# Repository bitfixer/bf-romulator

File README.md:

# bf-romulator
Romulator - RAM/ROM replacement and debug for 6502 and Z80 CPU systems

romulator - verilog code to implement ROMulator RAM/ROM replacement

programmer - programmer and console application for updating ROMulator, and debug

tools - C++ tools for building firmware images for ROMulator

## About

The ROMulator is a RAM/ROM replacement device for 6502 and Z80 systems, with programmable memory maps and debug functionality which allows you to halt a running CPU and read from or write to memory. See https://bitfixer.com/romulator for more information.

This Readme mostly covers the 6502 version for now, more documentation coming soon for Z80.

## Installation

To use the ROMulator, first remove the 6502 CPU from its socket on the PET (or other computer)'s motherboard.
**Note the orientation of the notch on the 6502 chip in the socket.**
Insert the 6502 chip into the 40-pin socket on the ROMulator board. Make sure the notch on the chip is aligned with the notch on the ROMulator socket.
Then, take the ROMulator board, and using the pins on the underside of the board, insert it into the 6502 socket on the motherboard.
**Make sure the notch on the 6502 chip is pointing in its original direction.**
If the ROMulator is inserted backwards, this may damage the ROMulator board since 5v will be presented where it shouldn't be.
Just make sure to double check:
- Original orientation of 6502
- 6502 chip notch should match with notch in ROMulator socket
- When inserting ROMulator into 6502 socket, 6502 chip should be in its original orientation

## Default Switch Settings

The ROMulator supports up to 32 memory maps. The default memory maps shipped with the ROMulator are currently mostly related to the Commodore PET, but you can add any maps you want via the programming interface. Over time more configurations for common 6502 computers will be added. Please note that these settings reflect the head commit of the repository, and may differ from the default settings on your ROMulator depending on when it was programmed. Building the latest version with `make program` after a `git pull` will generate the settings as described.
The default switch settings are as follows:

|Set Index  |Setting                                        |Switch 1   |Switch 2   |Switch 3   |Switch 4   |
|-----------|-----------------------------------------------|-----------|-----------|-----------|-----------|
|0          |BASIC 2, NON-CRTC, Business Kbd  (i.e. 2001)   |Off        |Off        |Off        |Off        |
|1          |BASIC 4, NON-CRTC  (i.e. 2001)                 |On         |Off        |Off        |Off        |
|2          |BASIC 4, CRTC, 80C (i.e. 8032)                 |Off        |On         |Off        |Off        |
|3          |BASIC 4, CRTC, 40C (i.e. 4032,4016)            |On         |On         |Off        |Off        |
|4          |BASIC 4, PET 4032 60Hz                         |Off        |Off        |On         |Off        |
|5          |BASIC 2, NON-CRTC, Normal Kbd (i.e. 2001)      |On         |Off        |On         |Off        |
|6          |BASIC 4, PET 4032 50Hz                         |Off        |On         |On         |Off        |
|7          |BASIC 4, PET 4016 60Hz                         |On         |On         |On         |Off        |
|8          |Apple II plus                                  |Off        |Off        |Off        |On         |
|9          |BASIC 1, PET 2001-8                            |On         |Off        |Off        |On         |
|10         |VIC-20 PAL                                     |Off        |On         |Off        |On         |
|11         |VIC-20 NTSC                                    |On         |On         |Off        |On         |
|12         |NOP Generator                                  |Off        |Off        |On         |On         |
|13         |PETTESTER                                      |On         |Off        |On         |On         |
|14         |PET Low RAM Test                               |Off        |On         |On         |On         |
|15         |PET RAM/ROM/VRAM Test                          |On         |On         |On         |On         |

The memory maps are defined in [config/memory_set_default.csv](config/memory_set_default.csv).
This file indicates which ROMs are located at which memory address.

## Adding Configurations for New 6502 Machines

This topic is big enough to have its own readme, and it is located here:\
[config/README.md](config/README.md)

## Program / Debug

Programming and Debugging with the ROMulator can be done in one of two ways:
- using a Raspberry Pi connected to the ROMulator's 10-pin header, or
- using a standalone programmer consisting of a D1 Mini Board (dev board for ESP12 wifi microcontroller module) and an interface board for connecting to the ROMulator. This method allows uploading new firmware over a wifi network as well as a direct connection to a Win/Linux/Mac using usb.

### Program / Debug with Standalone Programmer over WiFi or USB
Information on programming and debugging using the standalone programmer can be found here:\
[ROMULATOR_STANDALONE.md](ROMULATOR_STANDALONE.md)

### Program / Debug with Raspberry Pi
Programming or Debug functionality of the ROMulator uses a Raspberry Pi using a soft SPI implementation. 
You can use the optional RPI ROMulator programming board, or directly connect the following RPI physical pins to the corresponding pins on the 10-pin header on the ROMulator FPGA board:

|RPI     |FPGA Hdr|FPGA Hdr |RPI |
|--------|--------|---------|----|
|19      |1 (MOSI)|2 (3.3v) |17  |
|24      |3 (CS)  |4 (DBG)  |36  |
|22      |5 (RST) |6 (CDONE)|11  |
|23      |7 (SCK) |8        |NC  |
|21      |9 (MISO)|10 (GND) |34  |

If you are only programming and not running the debug client, DBG and CDONE are optional.
Take a look at this wiring diagram for a visual aid:

# ROMulator programming board

The optional RPI ROMulator programming board is just a breakout board for SPI and UART on the Pi which brings SPI0 and SPI1 pins out to separate headers, as well as a UART header. The ROMulator only uses the SPI0 header. If you received a kit for this board, here are a few quick notes on the assembly.
1. Solder header pins onto the TOP of the board in the section marked 'SPI0'.
2. Solder a 2-pin header onto the header section directly adjacent to SPI0.
3. Solder the 2x20 socket onto the BOTTOM of the board.
4. Connect the jumper onto the 2-pin header for programming. Remove for debug.
5. When attaching the board to the raspberry pi, the headers face away from the body of the raspberry pi. Depending on how the connectors are attached to the ribbon cable, it may be connected in one of two ways. Just make sure there is no twist in the cable. See these images for reference:

<table>
  <tr>
    <td>If your cable looks like this:</td>
    <td>Connect it like this.</td>
  </tr>
  <tr>
    <td></td>
    <td></td>
  </tr>
</table>

Or,

<table>
  <tr>
    <td>If your cable looks like this:</td>
    <td>Connect it like this.</td>
  </tr>
  <tr>
    <td></td>
    <td></td>
  </tr>
</table>

Please follow this procedure to enter debug mode on the romulator and read the contents of a running CPU.
1. run ```make bin/console``` from bf-romulator directory
2. run ```make debug``` to set appropriate pin directions on the pi. Specifically, this sets the DBG line to 1 to allow the ROMulator to start and not be stuck in a halt state, and sets the RST line to an input to avoid holding the fpga in reset.
3. If you are using the optional RPI programming board, remove the programming jumper.
4. run ```bin/console -r > output.bin``` to halt the cpu and read the full memory map into a file called output.bin.

### Installation

To install the ROMulator software on a Raspberry PI for programming or debug, download the script [setup.sh](https://raw.githubusercontent.com/bitfixer/bf-romulator/master/setup.sh) onto your Pi and execute from your home directory.
This will install the prequisites and fetch the latest version of the code in this repo.

The one-liner for this on the command line is:\
```wget -O - https://raw.githubusercontent.com/bitfixer/bf-romulator/master/setup.sh | sudo bash```

### Programming

To program a new firmware onto the ROMulator, run\
```make program```\
from the ~/bf-romulator directory.

Note that you will need all of the roms present in order to complete the build.\
This means that every unique rom specified in [config/memory_set_default.csv](config/memory_set_default.csv) to be present in the bf-romulator/roms directory.\
For convenience if you are downloading ROM images from a single source, there is a script which will do this for you.\
If you were downloading every rom with the base url of http://bitfixer.com, you would run the command:\
```BASEURL=http://bitfixer.com make fetch_roms```\
This downloads every unique rom specified in [config/memory_set_default.csv](config/memory_set_default.csv) to the roms directory.

## Programming Custom Firmware

If you just want to program a custom .bin file (if I send you one, for example) the procedure is a bit simpler.
Before the first time doing this run\
```make bin/programmer_spi```\
from the ~/bf-romulator directory.

Then, copy the custom .bin file somewhere on your raspberry pi, and run\
```bin/programmer_spi < customfirmware.bin```\
from the ~/bf-romulator directory, replacing customfirmware.bin with the actual path of that file.

## Virtual Display

A recent feature added to the ROMulator is the ability to create a virtual external display, using a connected Raspberry Pi as a webserver. By pointing a browser to the pi server, you will be able to 'see' the contents of video ram in realtime rendered into bitmap images.\
Currently, only the PET 2001 is supported, but other 6502 machines with memory-mapped graphics will be added soon.\
To use the virtual display feature on a PET 2001, connect the ROMulator to the 6502 socket on the pet, and connect the Pi via the interface board with the programming jumper OFF. For now only setting 1 (Sw 1 ON, rest OFF) is supported, which is BASIC 4.\
Power up the PET as usual, and the ROMulator LED should blink on for about one second. Then from the console on your Pi, from the bf-romulator directory, run:\
```make webserver```\
Then open a browser on another computer on the same network as the Pi, and navigate to the pi's server, like so:\
```http://raspberrypi.local:10000/canvas.html```\
Please note that while the pi will usually show up as raspberrypi.local, this is not always the case and you may need to know the actual local IP. At this point you should be able to enjoy a roughly 15-20 FPS PET 2001 display in your browser!

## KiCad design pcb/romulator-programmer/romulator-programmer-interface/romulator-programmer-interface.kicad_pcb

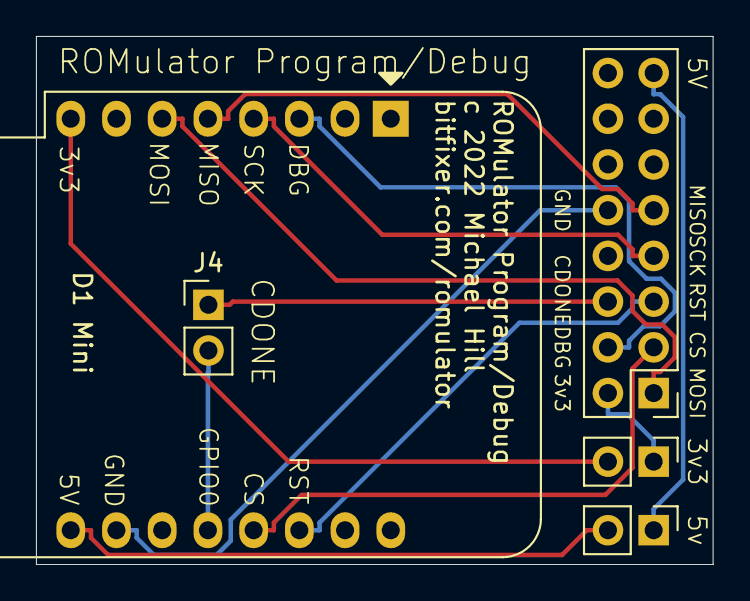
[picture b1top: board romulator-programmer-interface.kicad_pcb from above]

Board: 2 copper layers, 37.6 x 29.3 mm, 5 parts (0 on the bottom side), 13 nets.

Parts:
J1, J2, J4: Conn_01x02_Male; PinHeader_1x02_P2.54mm_Vertical
J3: Conn_02x08_Odd_Even; PinHeader_2x08_P2.54mm_Vertical
U1: WeMos_D1_mini; WEMOS_D1_mini_light

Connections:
3v3IN: J1.2, U1.8
5VIN: J2.2, U1.9
+3V3: J1.1, J3.2
+5V: J2.1, J3.15
CDONE: J3.6, J4.1
CS: J3.3, U1.13
DBG: J3.4, U1.3
GND: J3.10, U1.10
GPIO0: J4.2, U1.12
MISO: J3.9, U1.5
MOSI: J3.1, U1.6
RST: J3.5, U1.14
SCK: J3.7, U1.4

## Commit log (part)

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2020-01-21 installation script
2020-01-21 added verilog files
2020-01-21 added tools
2020-01-21 added pin constraints
2020-01-21 changed data_out to reg
2020-01-21 adding makefile
2020-01-21 added programmer
2020-01-21 updated common makefile
2020-01-21 updated makefile
2020-01-22 added romulator target
2020-01-22 removed unused files
2020-01-22 fixed makefile to prevent unnecessary rebuilds
2020-01-23 use full 64k maps
2020-01-23 increase to full 16 memory maps
2020-01-23 updated to 16 configurations
2020-01-23 fixed build_enable_table
2020-01-23 updated configuration size
2020-01-23 updated flash reader
2020-01-24 added GPL license
2020-01-24 license in Makefile
2020-01-24 added board schematics
2020-01-25 added rpi programming board schematic
2020-01-26 modified setup script
2020-01-26 fix table
2020-01-29 added reset option
2020-02-01 added README
2020-02-24 changed memory enable granularity
2020-02-24 change rom directory
2020-02-24 updated fetch_roms
2020-02-24 fixed dir
2020-02-24 change 9000-AFFF passthrough region
2020-02-25 fixed install script, apio seems to be broken at later version?
2020-02-25 slow down read on programmer, prevent bit errors
2020-02-26 added modified edit roms for 8032
2020-02-26 log readback
2020-02-27 changed programmer pins
2020-02-27 added readback
2020-02-28 fixed Makefile
2020-02-28 added make_screen_image
2020-02-28 mod screen image util
2020-02-29 added webserver, test option for make_screen_image
2020-03-01 tested image loading through web interface
2020-03-03 added testing files
2020-03-03 added console test
2020-03-03 fixed filename
2020-03-03 adjust timing of console
2020-03-04 Testing1 (#1)
    * added testing files
    * fixed makefile
    * added console test
    * fixed filename
    * adjust timing of console
2020-03-04 remove random bin during clean
2020-03-04 Change granularity 2 (#2)
    * changed memory enable granularity
    * remove random bin during clean
    * Makefile
2020-03-04 moved random_test.bin
2020-03-04 updated to physical pin numbers
2020-03-04 updated programming pins in README
2020-03-04 update 3v3 pin
2020-03-04 added stub for crc32
2020-03-04 WIP fpga does crc on debug
2020-03-04 fixed name
2020-03-04 size
2020-03-04 transfer dummy byte
2020-03-05 oops
2020-03-05 show crc32 of test binary
2020-03-05 report mismatch
2020-03-05 Crc32 (#3)
    * added stub for crc32
    * fixed syntax
    * WIP fpga does crc on debug
    * fixed name
    * size
    * transfer dummy byte
2020-03-05 add verification during memory write, retries for read
2020-03-23 added custom editor memory set
2020-03-24 added spi
2020-03-24 added 2001 normal keyboard option
2020-03-24 fixed rom
2020-04-07 updated switch settings
2020-04-07 Mhill/update readme (#4)
    * fixed rom
    * updated switch settings
2020-05-01 for pets without B000 rom, enable passthrough for B000-BFFF
2020-05-04 update apio version
2020-05-04 reboot after setup
2020-09-19 halt cpu while loading from flash
2020-09-19 added memory map for apple ii plus
2020-09-23 memory maps for apple ii plus
2020-09-24 fixed issue with memory reader, in some cases the next byte was sent before the previous was finished
2020-09-25 add debug mode to makefile
2020-09-25 added tool to verify rom dump from running system
2020-10-02 added a test rom for testing motherboard roms
2020-10-02 added zero page test
2020-10-02 added makefile for test rom
2020-10-04 ram check works
2020-10-04 makefile updates
2020-10-04 fixed
2020-10-04 added test_pet program to simplify test execution
2020-10-06 cleaned up testrom code
2020-10-06 updated testrom and console test program
2020-10-06 fixed test_pet bug
2020-10-06 cleanup on test_rom
2020-10-06 added apple ii test program
2020-10-06 fixed target for test_appleii
2020-10-22 changed url of submodule
2020-12-09 added rockwell aim-65 roms
2020-12-11 added 16k option for 4016
2021-01-08 added pin state to enable starting in debug
2021-02-24 added target for webserver
2021-02-24 simplify Makefile
2021-02-24 moved webserver
2021-02-24 fix makefile
2021-02-24 fix makefile2
2021-03-23 added settings for a PET 2001-8 board
2021-03-24 started test program for ram rom test
2021-03-24 more ram test stuff
2021-03-25 zero page test works
2021-03-25 more work on ram test, added pettest rom
2021-03-25 more mem test stuff
2021-03-25 swapped x and y flags
2021-03-25 separate flip
2021-03-25 added pages to test
2021-03-26 cleanup test rom
2021-03-26 added display to mem test
2021-03-27 cleaning up ram tester
2021-03-27 add config file
2021-03-27 fixed display of fault info
2021-03-28 added new rom and vram tester
2021-03-28 ramtest compilation works
2021-03-29 fixed fetch rom script
2021-03-29 added ram and rom tests to pet 2001 setup
2021-03-29 added nop generator
2021-03-31 add preinit
2021-03-31 show checksum for every 2048 bytes
2021-03-31 fixed edit rom on basic 2,4
2021-05-06 added diag tools
2021-05-06 ram test set text mode
2021-05-06 added wiring diagram for programming and debug
2021-05-12 updated diagram
2021-05-12 added kicad project with programming diagram
2021-05-18 fixed end address on ram test
2021-06-21 link to tools readme
2021-06-25 added apple ii plus
2021-06-25 fixed typo
2021-06-27 update default memory maps
2021-06-27 Update README.md
    more readme updates
2021-07-08 added ieee-488 test for PET
2021-07-13 image of rpi-romulator connection
2021-07-27 added clock generator files
2021-07-27 changed device
2021-07-28 added reset signal
2021-09-17 do not replace memory for PETTEST
2021-09-23 added vic-20 configurations
2021-09-23 added CONFIG variable to makefile, renamed default setting files
2021-09-23 added vic20 setting to default
2021-09-26 fixed vic-20 configuration, added pal and ntsc version
2021-10-01 update new names (#6)
2021-10-05 updated vic20 settings
2021-10-05 reading from vram is working
2021-10-07 write and read fram working
2021-10-07 add dual port ram
2021-10-07 added parity check for screen transfer
2021-10-08 added init file for vram
2021-10-09 set max of 2048 bytes for vram
2021-10-09 fix for vram sections in build_enable_table
2021-10-12 separate setup script for pi zero, without apio
2021-10-13 cleaned up warnings
2021-10-14 added make transfer
2021-10-14 fixed selection of vram address start and end
2021-10-14 separate libRomulatorDebug
2021-10-14 rebuilt console
2021-10-15 enable writing bmp files from web server
2021-10-15 testing image update speed
2021-10-15 make web server single thread for now
2021-10-17 add bitmap generation to webserver
2021-10-18 generating good images
2021-10-18 fixed SIGPIPE issue, handle broken pipe
2021-10-19 fixed reading 1024 bytes from vram
2021-10-19 added png writing
2021-10-19 makefile update
2021-10-20 added timer code
2021-10-20 added timing
2021-10-20 added thread for image encoding
2021-10-20 added canvas drawing
2021-10-21 add vram decoding to web
2021-10-21 scale up canvas
2021-10-22 updated webserver with cursor info
2021-10-22 add cursor information to vram
2021-10-22 use high bit for inverse, don't need cursor info anymore
2021-10-22 only send 1024 bytes of screen ram
2021-10-23 set vram size
2021-10-23 remove old console program
2021-10-23 FPS output for display
2021-10-26 Add vram support (#7)
    * reading from vram is working
    * write and read fram working
    * add dual port ram
    * added parity check for screen transfer
    * added re-sending for 8 byte blocks of vram
    * added init file for vram
2021-11-12 added vram section to setting 5
2021-11-17 add lookup table for character rom names
2021-11-20 webserver update
2021-11-20 Webserver character rom (#8)
    * add lookup table for character rom names
    * webserver update
2021-11-20 read config from rom request
2021-11-22 update location of config files
2021-11-22 moved readme for config files
2021-11-22 moved readme file to config
2021-11-22 fixed webserver
2021-11-22 allow webserver to run in bf-romulator directory
2021-11-23 simplified canvas scaling
2021-11-23 Instructions for virtual display
2021-11-23 transfer address 59468 on PET to indicate which character bank to use
2022-02-22 project for separate programming board
2022-02-22 romulator programming now works on d1 mini
2022-03-02 new adapters
2022-03-06 WIP code changes
2022-03-07 both programming and debug modes now working
2022-03-07 fixed programmer board layout
2022-03-07 WIP back to working on http server
2022-03-08 WIP programming from web server working
2022-03-08 refactor programming code
2022-03-09 uploading from web server with progress
2022-03-09 halt and read memory works
2022-03-09 debug write memory works
2022-03-11 WIP xmodem
2022-03-11 xmodem checksum working
2022-03-12 remove crc
2022-03-12 serial programming works
2022-03-14 vram reading now working
2022-03-15 display working for 8032
2022-03-15 generalize vram size calculations
2022-03-15 renamed xmodem files
2022-03-15 enable character rom read from config file
2022-03-17 allow switching config byte after halt
2022-03-17 some cleanup
2022-03-18 set config from web interface
2022-03-19 change config from pi console
2022-03-28 readme update
2022-03-28 pull and build wiringpi from repo, package is gone
2022-03-29 enable switching configs on d1 board
2022-03-29 added silkscreen on programmer pcb
2022-03-29 fixed build, server.h filename was confusing compiler
2022-03-30 use 32 configurations
2022-04-02 linux setup script v1
2022-04-02 added linux setup script
2022-04-03 chmod setup_linux.sh
2022-04-03 setup script for mac
2022-04-04 Update setup_pizero.sh
    update for pi zero install script, build wiring pi from source since package is gone
2022-04-07 readme update, and add redirect server access
2022-04-20 removed trailing slashes
2022-05-10 turned on pullups on data lines, fixed console build line
2022-05-11 WIP z80 stuff
2022-05-12 trying to load enable table from flash
2022-05-12 WIP loading enable table values
2022-05-12 loading enable table from flash now working
2022-05-12 only load the active configuration for the enable table
2022-05-13 WIP web uploader
2022-05-13 enable table working
2022-05-13 firmware download working
2022-05-13 index.php
2022-05-13 added error checking
2022-05-16 support changing config indicies up to 31 in console update READMEs for 32 config indicies move and rename some config files to match convention
2022-05-21 import everything from 6502
2022-05-21 WIP working state z80
2022-05-21 WIP ramenable table works
2022-05-21 WIP rwait signal test
2022-05-22 WIP working with RAM only, full load
2022-05-22 separate input module
2022-05-23 separate z80 config
2022-05-25 replace fetch_roms script
2022-05-30 support changing config indicies up to 31 in console (#10)
    update READMEs for 32 config indicies
    move and rename some config files to match convention
2022-05-30 separate input modules for z80 and 6502
2022-05-30 removed separate romulator_z80 dir
2022-05-30 removing reference to enable_table.txt
2022-06-13 WIP standalone config
2022-06-13 fixed bus enable, cpu now running in standalone mode
2022-06-13 switch standalone with dip switch 7
2022-06-21 added entries for trs80 m1 and ts 2068
2022-06-22 new make targets for z80, clean up trs-80 model 1 config
2022-06-22 fix issue with debug line preventing romulator from starting
2022-07-10 webserver: use SO_REUSEADDR to not be blocked by TIME_WAIT
    This allows the webserver to be immediately restarted when it was
    stopped and not having to wait for the local port to be available
    again while it is in TIME_WAIT state.
2022-07-10 webserver: fix png generation
    This fixes the crash when generating the screenshot on the
    server side and no character rom was specified on the command
    line by reading the character rom from the configuration instead.
2022-07-10 webserver: send last known good vram image on any read error
    This sends back the last known good vram image on read error to avoid
    flickering. Also declare any read-error as failure even though a retry
    is successfull, as it seems there is a problem with the retry-
    implementation somewhere.
2022-08-20 fix parsing bug in web programmer
2022-08-21 programmer fixes
2022-08-31 remove romulator.bin after programming
2022-10-10 validate user wifi settings, avoid accessing random data
2023-09-07 lower fpga speed to 24MHz to meet build requirements. Try to restore 48MHz soon
2023-09-07 try using slower clock for diagnostics
2023-09-07 use slower clock for diagnostics, fix timing issue and restore 48MHz clock
2023-09-13 fix to fetch_roms
2023-12-23 add delay to ice reset in programmer utility
2024-05-25 add reset before programming, prevents timeout crash
2024-05-26 WIP zmodem
